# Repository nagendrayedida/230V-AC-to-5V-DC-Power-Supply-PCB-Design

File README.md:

#230V AC to 5V DC Power Supply PCB Design

#Description:
This project is a PCB design that converts **230V AC to 5V DC** using KiCad. It includes schematic design, PCB layout, routing, and ground plane implementation.

#Features include:
* 2-layer PCB design
* Proper component placement and routing
* Ground plane for stability
* Designed with high-voltage isolation

#Block Diagram:
230V AC → Rectifier → Filter → Regulator → 5V DC Output.

#Files Included:
* Schematic
* PCB Layout
* Gerber & Drill Files
* Images

#Applications:
Embedded systems, IoT devices, low-power electronics.

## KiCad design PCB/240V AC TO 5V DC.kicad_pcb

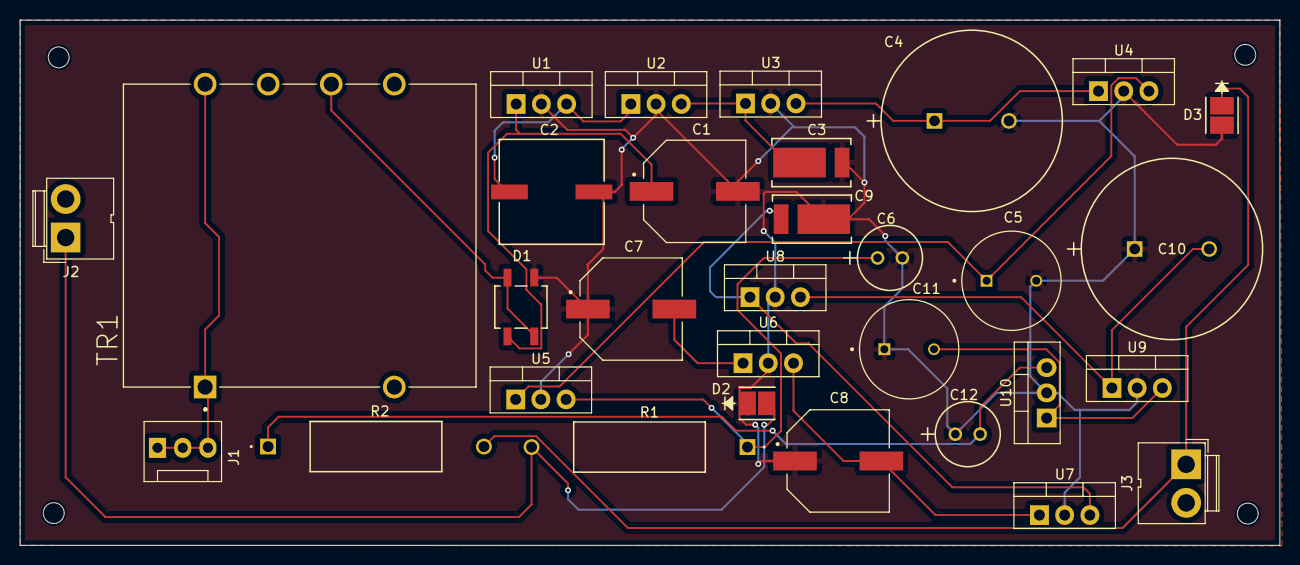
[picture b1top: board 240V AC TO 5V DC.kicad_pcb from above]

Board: 2 copper layers, 126.9 x 52.9 mm, 31 parts (0 on the bottom side), 17 nets.

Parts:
C1, C7: 79uf; CAP_25SVPD82M
C2: 132uf; CAP_0020F12_VIS
C3, C9: 212uf; A700W227M002ATE006
C4, C10: 353uf; EGXF101ELL681MM35S
C5, C11: 530uf; CAPPRD500W60D1000H3150
C6, C12: 636uf; RS80J681MCN1
C8: 132uf; CAP_25SVPD82M
D1: BRIDGE; REC-KMB14F
D2, D3: LED; LED-HSMG-A100-K42J2
J1: 240V AC; FanPinHeader_1x03_P2.54mm_Vertical
J2, J3: Conn_01x02_Pin; JWT_A3963_1x02_P3.96mm_Vertical
R1, R2: 100E; RES-AC03000001000JAC00
TR1: 40V AC; TR-XFMR_F28-085-C2
U1: 7824; TO-220-3_Vertical
U2: 7815; TO-220-3_Vertical
U3: 7809; TO-220-3_Vertical
U4: 7806; TO-220-3_Vertical
U5: 7805; TO-220-3_Vertical
U6: 7924; TO-220-3_Vertical
U7: 7915; TO-220-3_Vertical
U8: 7909; TO-220-3_Vertical
U9: 7906; TO-220-3_Vertical
U10: 7905; TO-220-3_Vertical

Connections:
/40VAC: D1.2, D1.4, TR1.7
/40vdc: C1.1, D1.1 (+), U1.1 (VI)
/230VAC: J1.1, J1.2, J1.3, TR1.1, TR1.5
/+5vdc: C6.1, R1.1, U5.3 (VO)
/+6vdc: C5.1, U4.3 (VO), U5.1 (VI)
/+9vdc: C4.1, U3.3 (VO), U4.1 (VI)
/+15vdc: C3.1, U2.3 (VO), U3.1 (VI)
/+24vdc: C2.1, U1.3 (VO), U2.1 (VI)
/-5vdc: C12.2, R2.1, U10.3 (VO)
/-6vdc: C11.2, U9.3 (VO), U10.1 (VI)
/-9vdc: C10.2, U8.3 (VO), U9.1 (VI)
/-15vdc: C9.2, U7.3 (VO), U8.1 (VI)
/-40vdc: C7.2, U6.1 (VI)
GND: C1.2, C2.2, C3.2, C4.2, C5.2, C6.2, C7.1, C8.1, C9.1, C10.1, C11.1, C12.1, D1.3 (-), D2.1 (K), D3.2 (A), U1.2 (GND), U2.2 (GND), U3.2 (GND), U4.2 (GND), U5.2 (GND), U6.2 (GND), U7.2 (GND), U8.2 (GND), U9.2 (GND), U10.2 (GND)
unnamed: D2.2 (A), J2.1, R1.2
unnamed: D3.1 (K), J3.1, R2.2
unnamed: C8.2, U6.3 (VO), U7.1 (VI)

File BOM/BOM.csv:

"Reference","Qty","Value","DNP","Exclude from BOM","Exclude from Board","Footprint","Datasheet"
"C1,C7","2","79uf","","","","Library:CAP_25SVPD82M","~"
"C2","1","132uf","","","","Library:CAP_0020F12_VIS","~"
"C3,C9","2","212uf","","","","Library:A700W227M002ATE006","~"
"C4,C10","2","353uf","","","","Library:EGXF101ELL681MM35S","~"
"C5,C11","2","530uf","","","","Library:CAPPRD500W60D1000H3150","~"
"C6,C12","2","636uf","","","","Library:RS80J681MCN1","~"
"C8","1","132uf","","","","Library:CAP_25SVPD82M","~"
"D1","1","BRIDGE","","","","Library:REC-KMB14F","https://www.vishay.com/docs/88769/woo5g.pdf"
"D2,D3","2","LED","","","","Library:LED-HSMG-A100-K42J2","~"
"J1","1","240V AC","","","","Connector:FanPinHeader_1x03_P2.54mm_Vertical","~"
"J2,J3","2","Conn_01x02_Pin","","","","Connector:JWT_A3963_1x02_P3.96mm_Vertical","~"
"R1,R2","2","100E","","","","Library:RES-AC03000001000JAC00","~"
"TR1","1","40V AC","","","","Library:TR-XFMR_F28-085-C2","http://www.breve.pl/pdf/ANG/TEZ_ang.pdf"
"U1","1","7824","","","","Package_TO_SOT_THT:TO-220-3_Vertical","https://www.ti.com/lit/ds/symlink/lm2931-n.pdf"
"U2","1","7815","","","","Package_TO_SOT_THT:TO-220-3_Vertical","https://www.ti.com/lit/ds/symlink/lm2931-n.pdf"
"U3","1","7809","","","","Package_TO_SOT_THT:TO-220-3_Vertical","https://www.ti.com/lit/ds/symlink/lm2931-n.pdf"
"U4","1","7806","","","","Package_TO_SOT_THT:TO-220-3_Vertical","https://www.ti.com/lit/ds/symlink/lm2931-n.pdf"
"U5","1","7805","","","","Package_TO_SOT_THT:TO-220-3_Vertical","https://www.ti.com/lit/ds/symlink/lm2931-n.pdf"
"U6","1","7924","","","","Package_TO_SOT_THT:TO-220-3_Vertical","https://www.ti.com/lit/ds/symlink/lm2931-n.pdf"
"U7","1","7915","","","","Package_TO_SOT_THT:TO-220-3_Vertical","https://www.ti.com/lit/ds/symlink/lm2931-n.pdf"
"U8","1","7909","","","","Package_TO_SOT_THT:TO-220-3_Vertical","https://www.ti.com/lit/ds/symlink/lm2931-n.pdf"
"U9","1","7906","","","","Package_TO_SOT_THT:TO-220-3_Vertical","https://www.ti.com/lit/ds/symlink/lm2931-n.pdf"
"U10","1","7905","","","","Package_TO_SOT_THT:TO-220-3_Vertical","https://www.ti.com/lit/ds/symlink/lm2931-n.pdf"

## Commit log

2026-03-19 Create temp
2026-03-19 Create PCB
2026-03-19 Create tem
